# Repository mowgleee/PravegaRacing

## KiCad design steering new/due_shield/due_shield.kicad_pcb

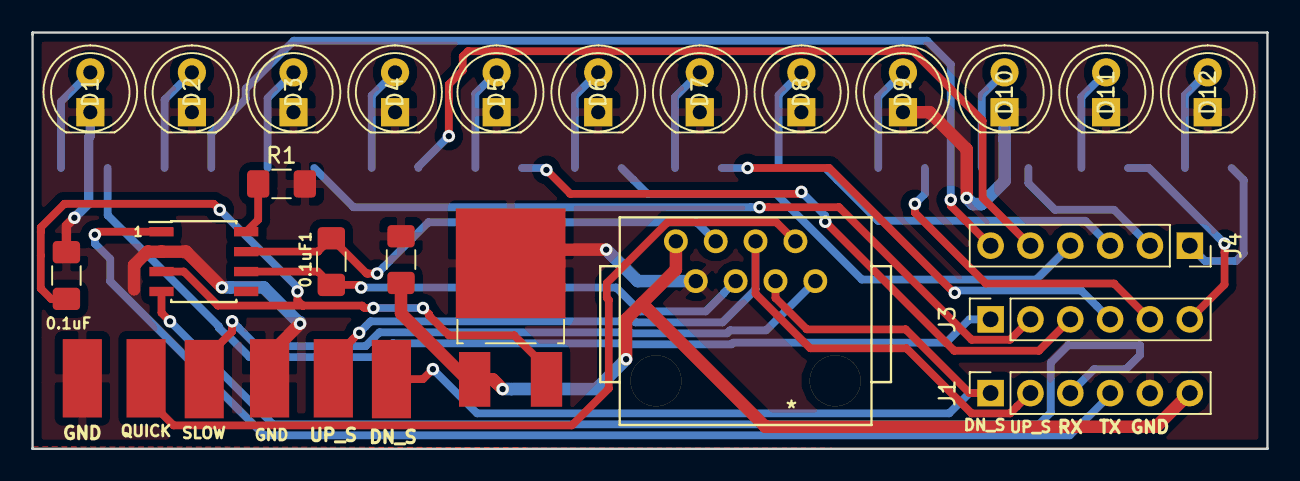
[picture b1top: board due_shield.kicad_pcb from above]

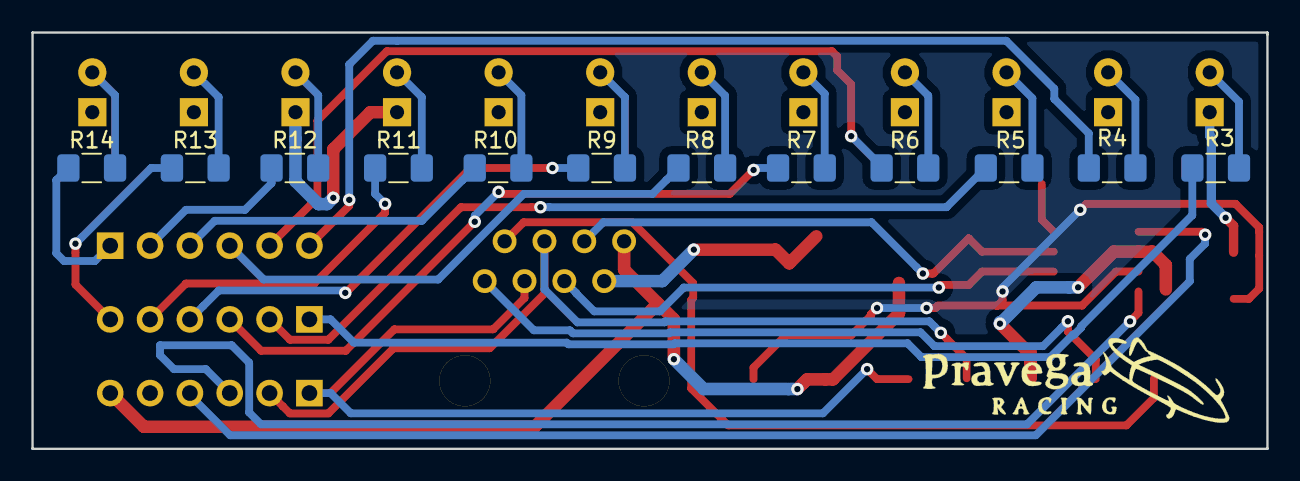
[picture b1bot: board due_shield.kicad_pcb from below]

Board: 2 copper layers, 78.7 x 26.5 mm, 30 parts (12 on the bottom side), 26 nets.

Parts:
0.1uF, 0.1uF1: C; C_1206_3216Metric_Pad1.42x1.75mm_HandSolder
D1, D2, D3, D4, D5, D6, D7, D8, D9, D10, D11, D12: LED; LED_D5.0mm
J1, J3, J4: Conn_01x06_Male; PinSocket_1x06_P2.54mm_Vertical
R1, R3, R4, R5, R6, R7, R8, R9, R10, R11, R12, R13, R14: R; R_1206_3216Metric_Pad1.42x1.75mm_HandSolder

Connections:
GND: 0.1uF.2, 0.1uF1.2, D1.1, D2.1, D3.1, D4.1, D5.1, D6.1, D7.1, D8.1, D9.1, D10.1, D11.1, D12.1, J1.5, R1.2
LED1: J3.1, R3.2
LED2: J3.2, R5.2
LED3: J3.3, R7.2
LED4: J3.4, R9.2
LED5: J3.5, R11.2
LED6: J3.6, R13.2
LED7: J4.1, R14.2
LED8: J4.2, R12.2
LED9: J4.3, R10.2
LED10: J4.4, R8.2
LED11: J4.5, R6.2
LED12: J4.6, R4.2
unnamed: D1.2, R3.1
unnamed: D2.2, R4.1
unnamed: D3.2, R5.1
unnamed: D4.2, R6.1
unnamed: D5.2, R7.1
unnamed: D6.2, R8.1
unnamed: D7.2, R9.1
unnamed: D8.2, R10.1
unnamed: D9.2, R11.1
unnamed: D10.2, R12.1
unnamed: D11.2, R13.1
unnamed: D12.2, R14.1
VIN: 0.1uF1.1, J1.6

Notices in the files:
parts and their libraries:
Copyright 2016 Accelerated Designs. All rights reserved.
